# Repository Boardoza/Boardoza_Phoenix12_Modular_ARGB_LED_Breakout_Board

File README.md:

# Boardoza Phoenix12 Breakout Board

The **Boardoza Phoenix12** is a compact **ring-shaped addressable RGB LED breakout board** featuring **12 individually controllable RGB LEDs** arranged in a circular layout with an open center. This unique geometry makes it especially suitable for creative lighting applications where uniform, circular illumination is required.

Designed to operate with both **3.3V and 5V power supplies**, the B-Phoenix12-BRK is fully compatible with a wide range of microcontrollers and digital systems. Thanks to its addressable LED architecture, each LED can be independently controlled in terms of color and brightness, enabling smooth animations, dynamic lighting effects, and customized visual outputs. The board is ideal for **photography and videography lighting**, **wearable electronics**, **decorative installations**, and **artistic or interactive projects**.

## [Click here to purchase!](https://www.ozdisan.com/ureticiler/boardoza)
| Front Side | Back Side |
|:---:|:---:|
|  |  |

---

## Key Features

- **12x Addressable RGB LEDs:** Each LED can be individually controlled for color and brightness, enabling dynamic lighting effects and smooth animations.  
- **Ring-Shaped Open-Center Design:** Circular form factor optimized for camera, phone, and creative lighting applications.  
- **Wide Voltage Compatibility:** Operates with both 3.3 V and 5 V power supplies for flexible system integration.  
- **Modular & Expandable Structure:** Multiple boards can be daisy-chained to create larger and customizable lighting systems.  
- **Flexible Connection Options:** Supports both SMD and through-hole (THR) soldering pads for easy installation.  
- **TTL & CMOS Logic Compatible:** Ensures reliable operation with common microcontrollers and digital circuits.  
- **Creative Application Ready:** Ideal for photography lighting, wearable electronics, decorative projects, and visual art installations.

---

## Technical Specifications

**Model:** Phoenix12   
**Manufacturer:** Boardoza  
**Functions:** Addressable RGB LED Ring  
**Input Voltage:** 3.3 V / 5 V  
**LED Model:** T3A33BRG-H9C0002X1U1930   
**Number of LEDs:** 12  
**LED Type:** Individually addressable RGB LEDs  
**Logic Compatibility:** TTL & CMOS  
**Data Interface:** Serial Data & Clock (DIN / CIN / DOUT / COUT)  
**Daisy-Chain Support:** Yes  
**Operating Temperature:** -40 °C to +85 °C  
**Board Dimensions:** 39.97 mm × 39.95 mm  

---

## Board Pinout

### ( J1 ) Power Connector

| Pin Number | Pin Name | Description |
|:---:|:---:|---|
| 1 | VCC | Power Supply (3.3V / 5V) |

### ( J2 ) Power Connector

| Pin Number | Pin Name | Description |
|:---:|:---:|---|
| 1 | VCC | Power Supply (3.3V / 5V) |

### ( J3 ) Clock Output

| Pin Number | Pin Name | Description |
|:---:|:---:|---|
| 1 | COUT | Clock Output |

### ( J4 ) Data Output

| Pin Number | Pin Name | Description |
|:---:|:---:|---|
| 1 | DOUT | Serial Data Output |

### ( J5 ) Clock Input

| Pin Number | Pin Name | Description |
|:---:|:---:|---|
| 1 | CIN | Clock Input |

### ( J6 ) Data Input

| Pin Number | Pin Name | Description |
|:---:|:---:|---|
| 1 | DIN | Serial Data Input |

### ( J7 ) Ground

| Pin Number | Pin Name | Description |
|:---:|:---:|---|
| 1 | GND | Ground |

### ( J8 ) Ground

| Pin Number | Pin Name | Description |
|:---:|:---:|---|
| 1 | GND | Ground |

---

## Board Dimensions

---

## Step Files

[Boardoza Phoenix12.step](./assets/Phoenix12%20Step.step)

---

## Sensor Datasheet

[T3A33BRG Datasheet.pdf](./assets/Phoenix12%20Datasheet.pdf)

---

## Version History

- **V1.0.0** – Initial Release

---

## Support

- If you have any questions or need support, please contact **support@boardoza.com**

---

## **License**

This repository contains both hardware and software components:

### **Hardware Design**

[![CC BY-SA 4.0][cc-by-sa-shield]][cc-by-sa]

All hardware design files are licensed under [Creative Commons Attribution-ShareAlike 4.0 International License][cc-by-sa].

[cc-by-sa]: http://creativecommons.org/licenses/by-sa/4.0/
[cc-by-sa-shield]: https://img.shields.io/badge/License-CC%20BY--SA%204.0-lightgrey.svg

### **Software/Firmware**

[![BSD-3-Clause][bsd-shield]][bsd]

All software and firmware are licensed under [BSD 3-Clause License][bsd].

[bsd]: https://opensource.org/licenses/BSD-3-Clause
[bsd-shield]: https://img.shields.io/badge/License-BSD%203--Clause-blue.svg

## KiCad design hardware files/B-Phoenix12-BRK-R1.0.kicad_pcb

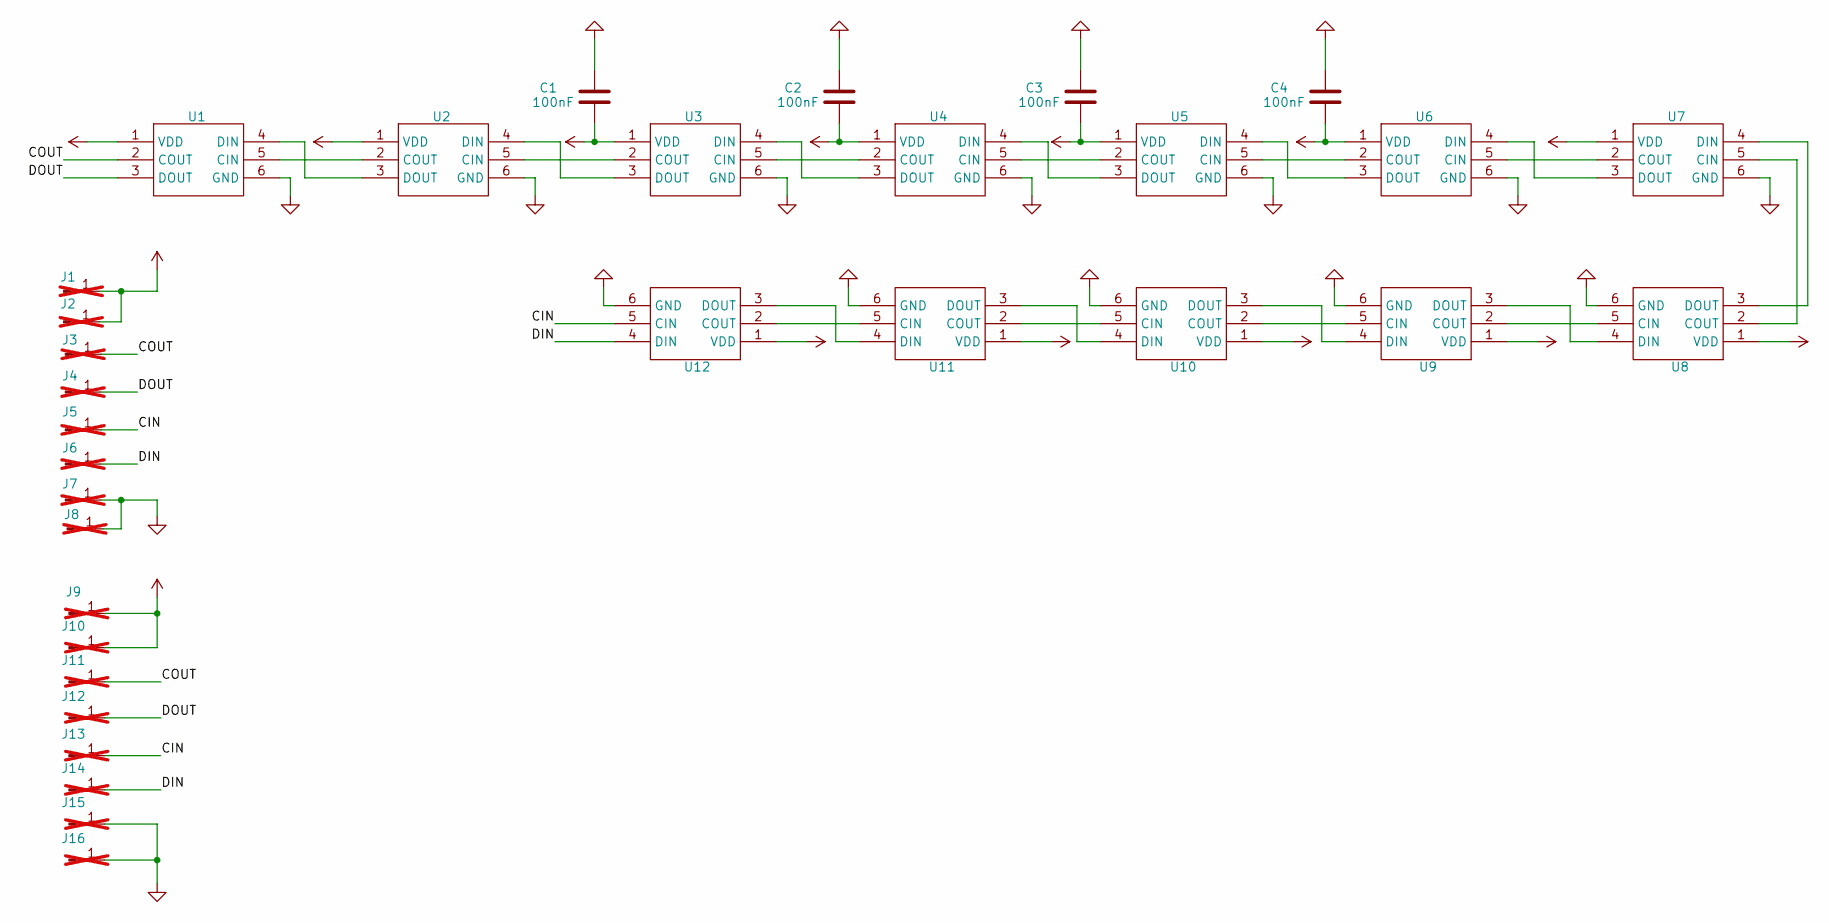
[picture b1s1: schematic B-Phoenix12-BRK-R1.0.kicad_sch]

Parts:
C1, C2, C3, C4: 100nF; C_0603_1608Metric; MPN MCF03KTB500104
J1, J2, J3, J4, J5, J6, J7, J8: Conn_01x01_Pin; PinHeader_1x01_P2.54mm_Vertical; not fitted
J9, J10, J11, J12, J13, J14, J15, J16: Conn_01x01_Pin; SolderWirePad_1x01_SMD_1x2mm; not fitted
U1, U2, U3, U4, U5, U6, U7, U8, U9, U10, U11, U12: T3A33BRG-H9C0002X1U1930_HVK; MPN T3A33BRG-H9C0002X1U1930

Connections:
/CIN: J5.1, J13.1, U12.5 (CIN)
/COUT: J3.1, J11.1, U1.2 (COUT)
/DIN: J6.1, J14.1, U12.4 (DIN)
/DOUT: J4.1, J12.1, U1.3 (DOUT)
GND: C1.1, C2.1, C3.1, C4.1, J7.1, J8.1, J15.1, J16.1, U1.6 (GND), U2.6 (GND), U3.6 (GND), U4.6 (GND), U5.6 (GND), U6.6 (GND), U7.6 (GND), U8.6 (GND), U9.6 (GND), U10.6 (GND), U11.6 (GND), U12.6 (GND)
unnamed: U1.5 (CIN), U2.2 (COUT)
unnamed: U1.4 (DIN), U2.3 (DOUT)
unnamed: U2.5 (CIN), U3.2 (COUT)
unnamed: U2.4 (DIN), U3.3 (DOUT)
unnamed: U3.5 (CIN), U4.2 (COUT)
unnamed: U3.4 (DIN), U4.3 (DOUT)
unnamed: U4.5 (CIN), U5.2 (COUT)
unnamed: U4.4 (DIN), U5.3 (DOUT)
unnamed: U5.5 (CIN), U6.2 (COUT)
unnamed: U5.4 (DIN), U6.3 (DOUT)
unnamed: U6.5 (CIN), U7.2 (COUT)
unnamed: U6.4 (DIN), U7.3 (DOUT)
unnamed: U7.5 (CIN), U8.2 (COUT)
unnamed: U7.4 (DIN), U8.3 (DOUT)
unnamed: U8.5 (CIN), U9.2 (COUT)
unnamed: U8.4 (DIN), U9.3 (DOUT)
unnamed: U10.5 (CIN), U11.2 (COUT)
unnamed: U9.5 (CIN), U10.2 (COUT)
unnamed: U10.4 (DIN), U11.3 (DOUT)
unnamed: U9.4 (DIN), U10.3 (DOUT)
unnamed: U11.5 (CIN), U12.2 (COUT)
unnamed: U11.4 (DIN), U12.3 (DOUT)
VCC: C1.2, C2.2, C3.2, C4.2, J1.1, J2.1, J9.1, J10.1, U1.1 (VDD), U2.1 (VDD), U3.1 (VDD), U4.1 (VDD), U5.1 (VDD), U6.1 (VDD), U7.1 (VDD), U8.1 (VDD), U9.1 (VDD), U10.1 (VDD), U11.1 (VDD), U12.1 (VDD)

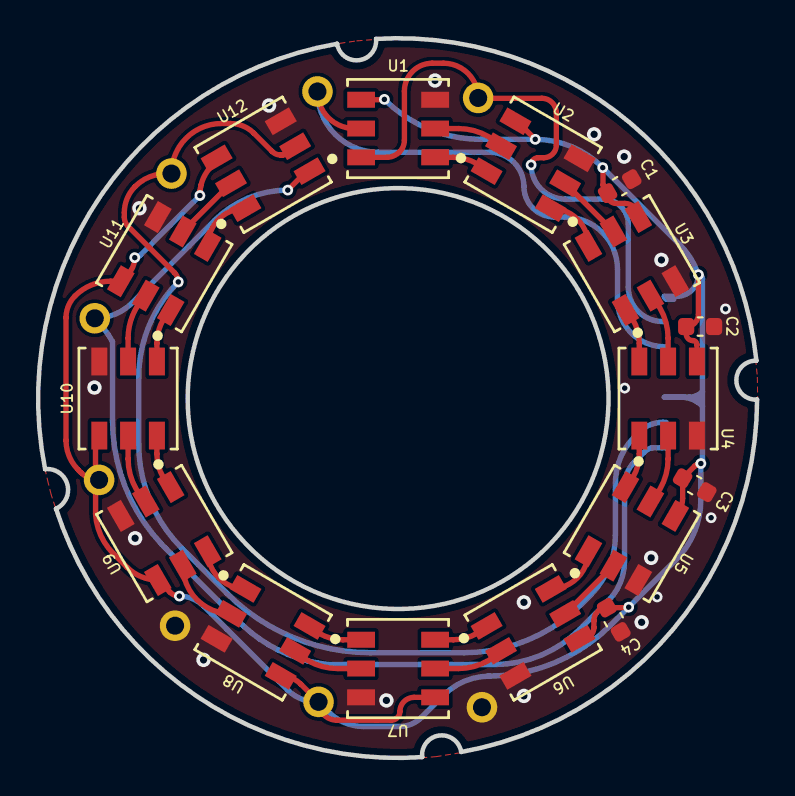
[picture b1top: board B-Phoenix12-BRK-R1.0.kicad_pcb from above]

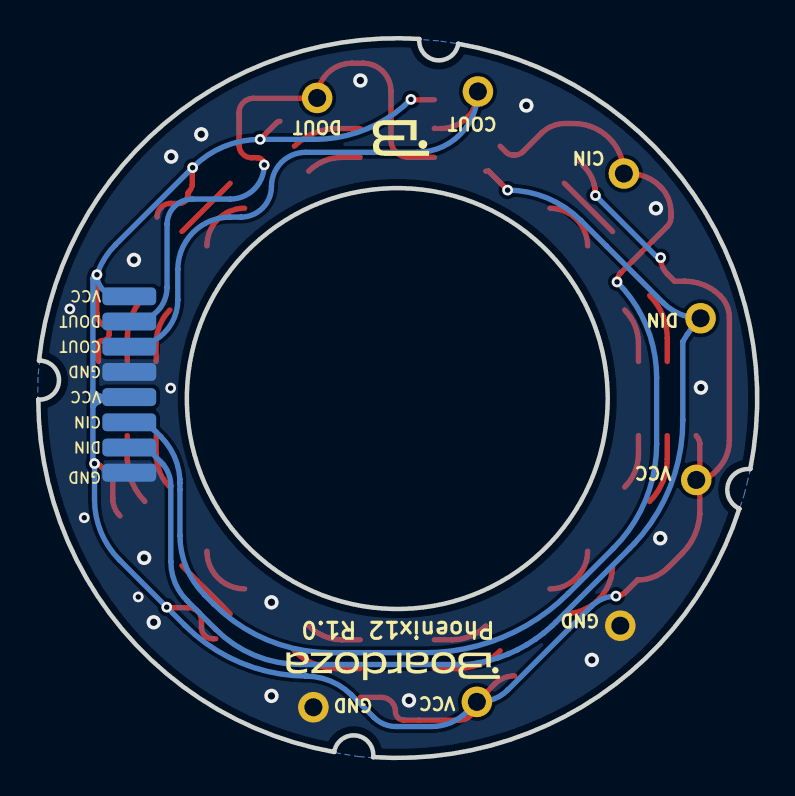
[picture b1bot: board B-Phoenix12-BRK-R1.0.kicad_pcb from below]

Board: 2 copper layers, 39.9 x 40.0 mm, 32 parts (8 on the bottom side), 28 nets.

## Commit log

2026-04-28 Fix hueOffset declaration formatting
2026-04-28 Fixed comment lines
